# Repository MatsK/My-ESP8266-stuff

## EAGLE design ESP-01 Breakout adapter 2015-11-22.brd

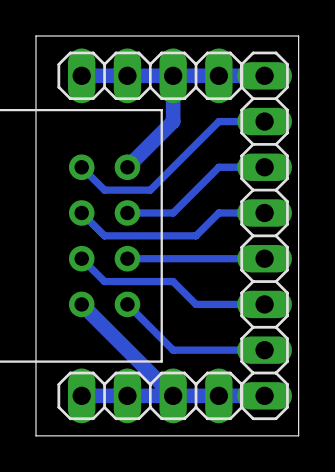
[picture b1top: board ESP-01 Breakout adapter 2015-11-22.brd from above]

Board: 2 copper layers, 14.6 x 22.2 mm, 4 parts (0 on the bottom side), 8 nets.

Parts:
ESP8266: ESP8266-01; ESP-01
JP1: 1X08
JP2, JP3: 1X04

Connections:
CH_PD: ESP8266.P$2, JP1.5
GND: ESP8266.P$8, JP1.8
GPIO0: ESP8266.P$6, JP1.4
GPIO2: ESP8266.P$7, JP1.6
RST: ESP8266.P$3, JP1.3
URXD: ESP8266.P$5, JP1.2
UTXD: ESP8266.P$1, JP1.7
VCC: ESP8266.P$4, JP1.1

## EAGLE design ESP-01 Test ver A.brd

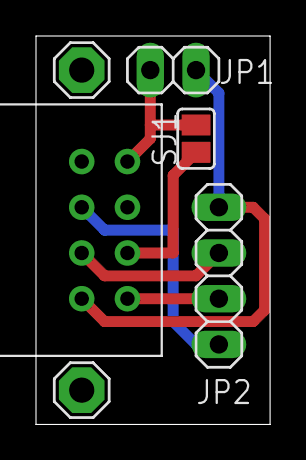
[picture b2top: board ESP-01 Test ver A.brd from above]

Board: 2 copper layers, 13.0 x 21.6 mm, 6 parts (0 on the bottom side), 6 nets.

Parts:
JP1: 1X02
JP2: 1X04
LSP1, LSP2: SE14
SJ1: SJ
U$1: ESP8266-01; ESP-01

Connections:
GND: JP1.2, JP2.4, U$1.P$8
unnamed: JP2.2, U$1.P$1
unnamed: SJ1.1, U$1.P$2
unnamed: JP1.1, SJ1.2, U$1.P$4
unnamed: JP2.3, U$1.P$7
unnamed: JP2.1, U$1.P$6

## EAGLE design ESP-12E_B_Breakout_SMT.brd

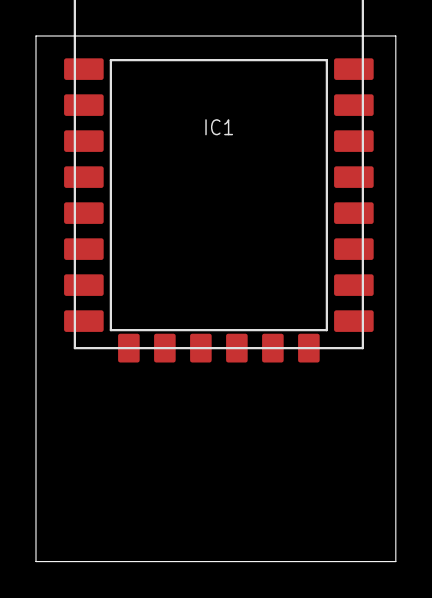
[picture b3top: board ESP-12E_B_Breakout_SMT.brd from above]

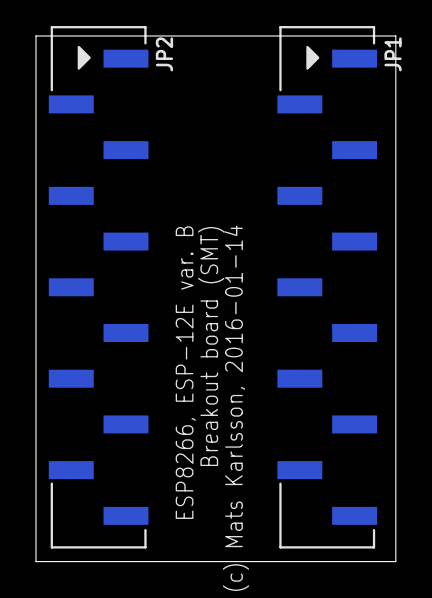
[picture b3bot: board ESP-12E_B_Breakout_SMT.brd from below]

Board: 2 copper layers, 20.0 x 29.2 mm, 3 parts (2 on the bottom side), 22 nets, no tracks yet.

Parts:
IC1: ESP8266-12E
JP1, JP2: 1X11_SMT

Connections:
ADC: IC1.2, JP1.2
CS: IC1.17, JP1.11
EN: IC1.3, JP1.3
GND: IC1.9, JP2.8
GPIO0: IC1.12, JP2.5
GPIO1(TX): IC1.16, JP2.1
GPIO2: IC1.11, JP2.6
GPIO3(RX): IC1.15, JP2.2
GPIO4: IC1.13, JP2.4
GPIO5: IC1.14, JP2.3
GPIO9: IC1.19, JP1.9
GPIO10: IC1.20, JP1.10
GPIO12: IC1.6, JP1.6
GPIO13: IC1.7, JP1.7
GPIO14: IC1.5, JP1.5
GPIO15: IC1.10, JP2.7
GPIO16: IC1.4, JP1.4
MISO: IC1.18, JP2.11
MOSI: IC1.21, JP2.10
RESET: IC1.1, JP1.1
SCK: IC1.22, JP2.9
VCC: IC1.8, JP1.8

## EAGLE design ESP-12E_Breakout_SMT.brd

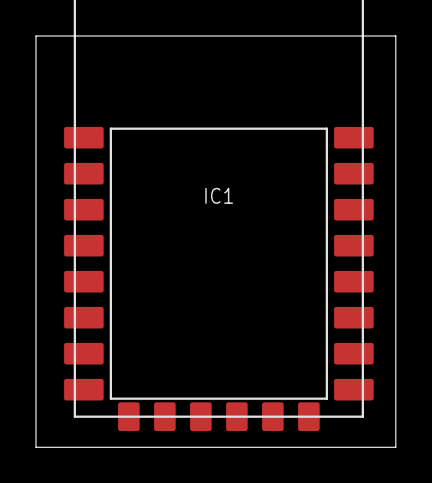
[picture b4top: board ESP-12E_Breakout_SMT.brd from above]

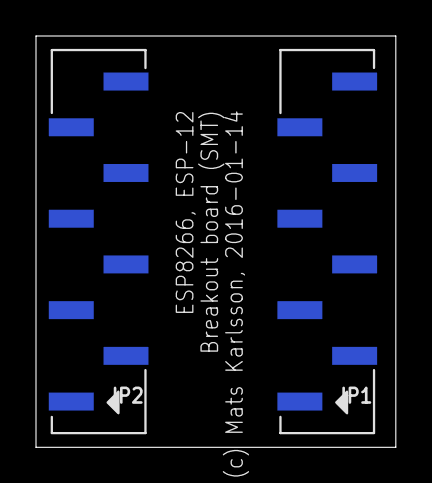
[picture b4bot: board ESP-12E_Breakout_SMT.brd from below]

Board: 2 copper layers, 20.0 x 22.9 mm, 3 parts (2 on the bottom side), 16 nets, no tracks yet.

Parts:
IC1: ESP8266-12E
JP1, JP2: 1X08_SMT

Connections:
ADC: IC1.2, JP1.7
EN: IC1.3, JP1.6
GND: IC1.9, JP2.1
GPIO0: IC1.12, JP2.4
GPIO1(TX): IC1.16, JP2.8
GPIO2: IC1.11, JP2.3
GPIO3(RX): IC1.15, JP2.7
GPIO4: IC1.13, JP2.5
GPIO5: IC1.14, JP2.6
GPIO12: IC1.6, JP1.3
GPIO13: IC1.7, JP1.2
GPIO14: IC1.5, JP1.4
GPIO15: IC1.10, JP2.2
GPIO16: IC1.4, JP1.5
RESET: IC1.1, JP1.8
VCC: IC1.8, JP1.1

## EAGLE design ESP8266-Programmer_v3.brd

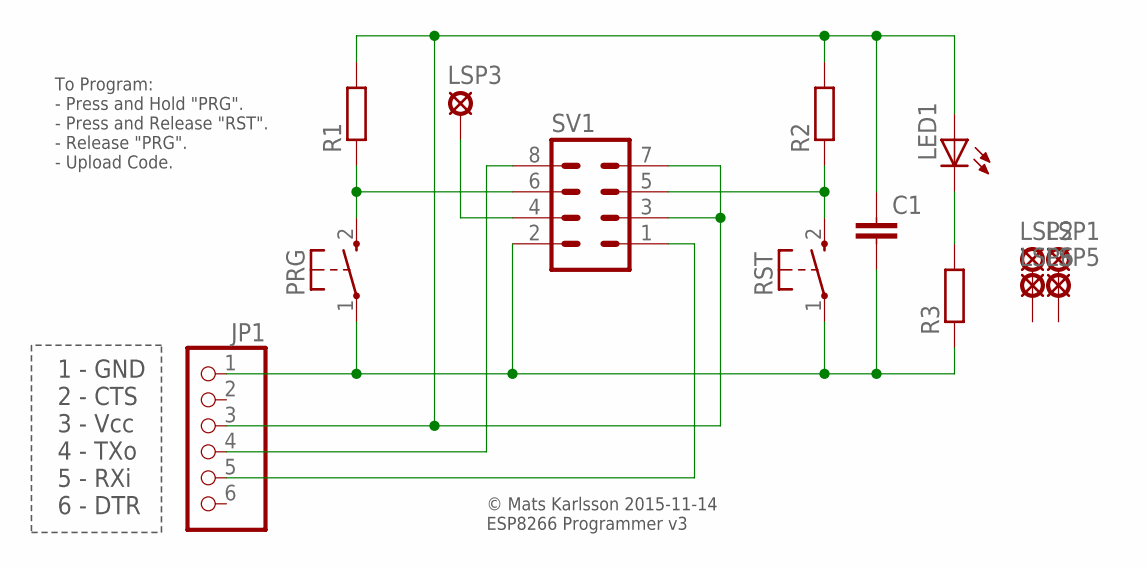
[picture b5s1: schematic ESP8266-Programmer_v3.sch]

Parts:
C1: C-EU025_050-035X075; C025_050-035X075
JP1: PINHD-1X6; 1X06
LED1: TLLG4400; LED3MM
LSP1, LSP2, LSP3, LSP5, LSP6: SE11
PRG: KSS-2EG4430
R1, R2: R-EU_0204/5; 0204/5
R3: R-EU_0204/7; 0204/7
RST: KSS-2EG4430
SV1: MA04-2

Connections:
unnamed: C1.2, JP1.1, PRG.1, R3.1, RST.1, SV1.2
unnamed: R2.1, RST.2 (S), SV1.5
unnamed: LSP3.MP, SV1.4
unnamed: JP1.4, SV1.8
unnamed: PRG.2 (S), R1.1, SV1.6
unnamed: C1.1, JP1.3, LED1.A, R1.2, R2.2, SV1.3, SV1.7
unnamed: JP1.5, SV1.1
unnamed: LED1.K (C), R3.2

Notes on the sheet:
1 - GND 2 - CTS 3 - Vcc 4 - TXo 5 - RXi 6 - DTR
© Mats Karlsson 2015-11-14 ESP8266 Programmer v3
To Program: - Press and Hold "PRG". - Press and Release "RST". - Release "PRG". - Upload Code.

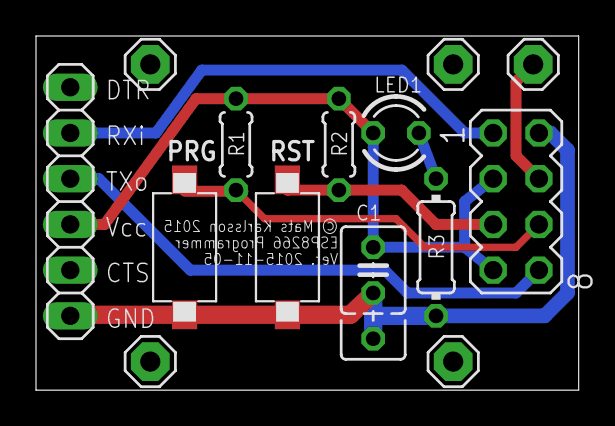
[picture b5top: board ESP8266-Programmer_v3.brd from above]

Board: 2 copper layers, 30.1 x 19.7 mm, 14 parts (0 on the bottom side), 8 nets.

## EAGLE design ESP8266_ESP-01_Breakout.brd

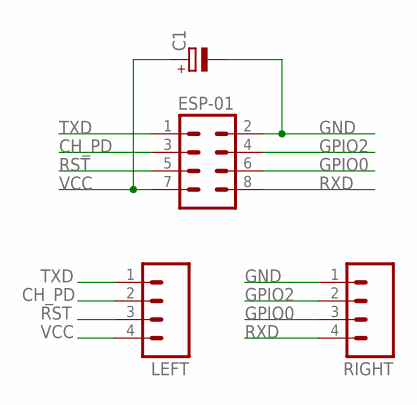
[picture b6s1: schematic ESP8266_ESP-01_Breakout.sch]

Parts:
C1: CPOL-EUB45181B; B45181B
ESP-01: M04X2; 2X4
LEFT: M04PTH; 1X04
RIGHT: M04PTH; 1X04

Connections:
CH_PD: ESP-01.3, LEFT.2
GND: C1.-, ESP-01.2, RIGHT.1
GPIO0: ESP-01.6, RIGHT.3
GPIO2: ESP-01.4, RIGHT.2
RST: ESP-01.5, LEFT.3
RXD: ESP-01.8, RIGHT.4
TXD: ESP-01.1, LEFT.1
VCC: C1.+, ESP-01.7, LEFT.4

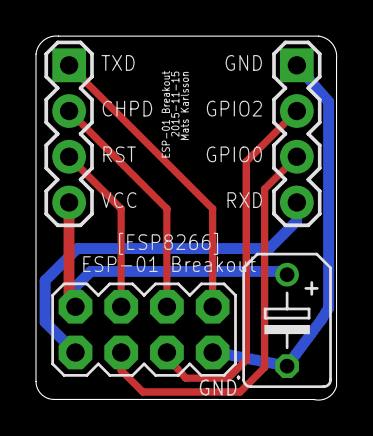
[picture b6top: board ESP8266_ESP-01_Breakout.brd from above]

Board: 2 copper layers, 16.7 x 20.2 mm, 4 parts (0 on the bottom side), 8 nets.

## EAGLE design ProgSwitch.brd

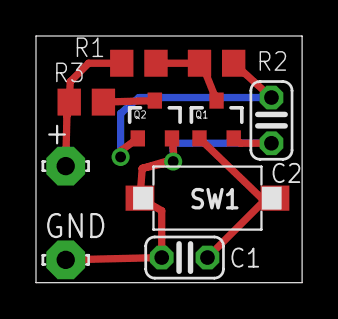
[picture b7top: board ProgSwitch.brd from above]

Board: 2 copper layers, 14.8 x 13.7 mm, 10 parts (0 on the bottom side), 6 nets.

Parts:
+: LSP10
C1: 100nF; C025-024X044
C2: 2u2F; C025-024X044
GND: LSP10
Q1, Q2: BSS138; SOT23-3
R1: 470K; R0805
R2: 100K; R0805
R3: R0805
SW1: KSS-2EG4430

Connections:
GND: C1.1, C2.1, GND.MP, Q1.2, Q2.2, SW1.1
GPIO0: Q2.3, R3.2
unnamed: Q1.3, R1.1, R2.1
unnamed: C2.2, Q2.1, R2.2
RESET: C1.2, Q1.1, SW1.2
VCC: +.MP, R1.2, R3.1

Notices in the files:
parts and their libraries:
SparkFun-Connectors: Licensing: CC v3.0 Share-Alike You are welcome to use this library for commercial purposes.
SparkFun-DiscreteSemi: Licensing: Creative Commons ShareAlike 4.0 International - https://creativecommons.org/licenses/by-sa/4.0
